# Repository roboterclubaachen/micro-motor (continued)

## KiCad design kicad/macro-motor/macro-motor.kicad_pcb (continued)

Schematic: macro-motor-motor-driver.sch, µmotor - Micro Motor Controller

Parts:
C301: >10µ 35V; CP_Radial_D8.0mm_P3.50mm
C302: 100n 50V; C_0603_1608Metric
C303: 100n 50V; C_0402_1005Metric
C304: 1µ 6V3 X7R; C_0402_1005Metric
C305: 1µ 16V X7R; C_0402_1005Metric
C306: 47n 50V X7R; C_0402_1005Metric
J301: A; PinHeader_1x02_P2.54mm_Vertical
J302: B; PinHeader_1x02_P2.54mm_Vertical
J303: C; PinHeader_1x02_P2.54mm_Vertical
JP301: SPC; SolderJumper-2_P1.3mm_Open_RoundedPad1.0x1.5mm
JP302: SPB; SolderJumper-2_P1.3mm_Open_RoundedPad1.0x1.5mm
JP303: SPA; SolderJumper-2_P1.3mm_Open_RoundedPad1.0x1.5mm
Q301, Q302, Q303: FDMD82xx; DFN-12-2EP_3.3x5mm_Pitch0.65mm
R301: 10k; R_0402_1005Metric
R302, R303, R304: 5m; R_0805_2012Metric
TP301: +24V; Pin_D1.0mm_L10.0mm
TP302: GND; Pin_D1.0mm_L10.0mm
TP303, TP304: UP; Pin_D1.0mm_L10.0mm
TP305: VP; Pin_D1.0mm_L10.0mm
TP306: VN; Pin_D1.0mm_L10.0mm
TP307: WP; Pin_D1.0mm_L10.0mm
TP308: WN; Pin_D1.0mm_L10.0mm
TP309: MOSI; Pin_D1.0mm_L10.0mm
TP310: MISO; Pin_D1.0mm_L10.0mm
TP311: SCK; Pin_D1.0mm_L10.0mm
TP312: ~CS; Pin_D1.0mm_L10.0mm
TP313, TP322: W; Pin_D1.0mm_L10.0mm
TP314, TP323: V; Pin_D1.0mm_L10.0mm
TP315, TP324: U; Pin_D1.0mm_L10.0mm
TP316: GH_U; Pin_D1.0mm_L10.0mm
TP317: GL_U; Pin_D1.0mm_L10.0mm
TP318: GH_W; Pin_D1.0mm_L10.0mm
TP319: GL_W; Pin_D1.0mm_L10.0mm
TP320: GH_V; Pin_D1.0mm_L10.0mm
TP321: GL_V; Pin_D1.0mm_L10.0mm
U301: DRV8323S; QFN-40-1EP_6x6mm_P0.5mm_EP4.6x4.6mm

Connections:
+3V3: R301.2, U301.24 (VREF); also elsewhere on the board
+24V: C301.1, C302.1, C303.1, C305.2, Q301.1 (D1), Q301.2, Q301.3, Q301.13 (D1), Q302.1 (D1), Q302.2, Q302.3, Q302.13 (D1), Q303.1 (D1), Q303.2, Q303.3, Q303.13 (D1), TP301.1, U301.4 (VM), U301.5 (VDRAIN); also elsewhere on the board
/Microcontroller/CS: TP312.1, U301.29 (~SCS); also elsewhere on the board
/Microcontroller/CurrentU: TP315.1, U301.23 (SOA); also elsewhere on the board
/Microcontroller/CurrentV: TP314.1, U301.22 (SOB); also elsewhere on the board
/Microcontroller/CurrentW: TP313.1, U301.21 (SOC); also elsewhere on the board
/Microcontroller/Fault: U301.25 (~FAULT); also elsewhere on the board
/Microcontroller/MISO: R301.1, TP310.1, U301.26 (SDO); also elsewhere on the board
/Microcontroller/MOSI: TP309.1, U301.27 (SDI); also elsewhere on the board
/Microcontroller/SCK: TP311.1, U301.28 (SCLK); also elsewhere on the board
/Motor_Driver/3V3_DRV: C304.2, U301.33 (DVDD)
/Motor_Driver/CPH: C306.2, U301.2 (CPH)
/Motor_Driver/CPL: C306.1, U301.1 (CPL)
/Motor_Driver/ENABLE: U301.30 (ENABLE); also elsewhere on the board
/Motor_Driver/GH_U: Q303.12 (G1), TP316.1, U301.6 (GHA)
/Motor_Driver/GH_V: Q302.12 (G1), TP320.1, U301.15 (GHB)
/Motor_Driver/GH_W: Q301.12 (G1), TP318.1, U301.16 (GHC)
/Motor_Driver/GL_U: Q303.4 (G2), TP317.1, U301.8 (GLA)
/Motor_Driver/GL_V: Q302.4 (G2), TP321.1, U301.13 (GLB)
/Motor_Driver/GL_W: Q301.4 (G2), TP319.1, U301.18 (GLC)
/Motor_Driver/IN_U_N: TP304.1, U301.35 (INLA); also elsewhere on the board
/Motor_Driver/IN_U_P: TP303.1, U301.34 (INHA); also elsewhere on the board
/Motor_Driver/IN_V_N: TP306.1, U301.37 (INLB); also elsewhere on the board
/Motor_Driver/IN_V_P: TP305.1, U301.36 (INHB); also elsewhere on the board
/Motor_Driver/IN_W_N: TP308.1, U301.39 (INLC); also elsewhere on the board
/Motor_Driver/IN_W_P: TP307.1, U301.38 (INHC); also elsewhere on the board
/Motor_Driver/OUT_U: Q303.7, Q303.8, Q303.9, Q303.10, Q303.11 (G1R), TP324.1, U301.7 (SHA); also elsewhere on the board
/Motor_Driver/OUT_V: Q302.7, Q302.8, Q302.9, Q302.10, Q302.11 (G1R), TP323.1, U301.14 (SHB); also elsewhere on the board
/Motor_Driver/OUT_W: Q301.7, Q301.8, Q301.9, Q301.10, Q301.11 (G1R), TP322.1, U301.17 (SHC); also elsewhere on the board
/Motor_Driver/VCP: C305.1, U301.3 (VCP)
GND: C301.2, C302.2, C303.2, C304.1, J303.2, R304.2, TP302.1, U301.10 (SNA), U301.31 (CAL), U301.32 (AGND), U301.40 (PGND), U301.41 (GND); also elsewhere on the board
unnamed: J301.1, JP301.2, Q301.5 (S2), Q301.6, Q301.14 (S2), R302.1
unnamed: J301.2, J302.2, J303.1, JP303.2, Q303.5 (S2), Q303.6, Q303.14 (S2), R302.2, R303.2, R304.1, U301.11 (SNB), U301.20 (SNC)
unnamed: J302.1, JP302.2, Q302.5 (S2), Q302.6, Q302.14 (S2), R303.1
unnamed: JP301.1, U301.19 (SPC)
unnamed: JP302.1, U301.12 (SPB)
unnamed: JP303.1, U301.9 (SPA)

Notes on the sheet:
Calibration can be done via SPI
Optional: SHx pins will be used for SPx (DRV8323S CSA_FET bit)
external capacitor >10µ 35V connected to pads

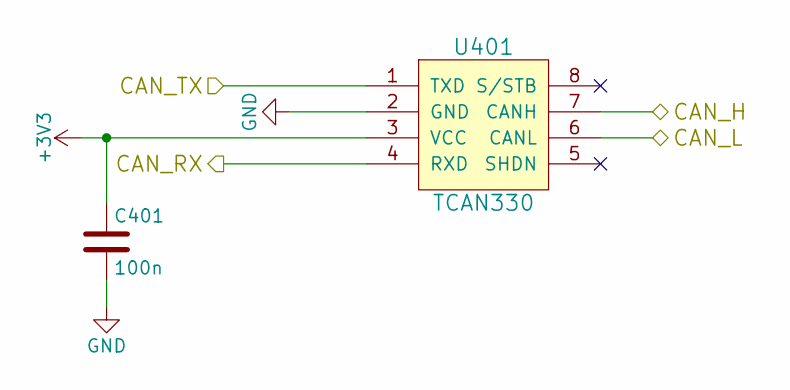
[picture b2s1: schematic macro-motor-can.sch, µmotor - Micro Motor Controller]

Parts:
C401: 100n; C_0402_1005Metric
U401: TCAN330; SOT-23-8

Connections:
+3V3: C401.1, U401.3 (VCC); also elsewhere on the board
/CAN/CAN_H: U401.7 (CANH); also elsewhere on the board
/CAN/CAN_L: U401.6 (CANL); also elsewhere on the board
/CAN/CAN_RX: U401.4 (RXD); also elsewhere on the board
/CAN/CAN_TX: U401.1 (TXD); also elsewhere on the board
GND: C401.2, U401.2 (GND); also elsewhere on the board

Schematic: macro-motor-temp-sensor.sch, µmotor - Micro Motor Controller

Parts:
C501: 100n; C_0402_1005Metric
J501: SCL; Pin_D1.0mm_L10.0mm
J502: SDA; Pin_D1.0mm_L10.0mm
J503: 3V3; Pin_D1.0mm_L10.0mm
J504: GND; Pin_D1.0mm_L10.0mm
R501, R502: 4k7; R_0402_1005Metric
U501: TMP006; WCSP-8_1.6x1.6mm_P0.5mm

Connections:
+3V3: C501.1, J503.1, R501.1, R502.1, U501.A3 (V+); also elsewhere on the board
/Microcontroller/I2C_SCL: J501.1, R501.2, U501.B3 (SCL); also elsewhere on the board
/Microcontroller/I2C_SDA: J502.1, R502.2, U501.C3 (SDA); also elsewhere on the board
GND: C501.2, J504.1, U501.A1 (DGND), U501.A2 (AGND), U501.B1 (ADR1), U501.C1 (ADR0); also elsewhere on the board

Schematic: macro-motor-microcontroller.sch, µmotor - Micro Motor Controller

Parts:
C601, C602, C603: 100n; C_0402_1005Metric
D601: Blue; LED_0402_1005Metric
D602: Red; LED_0402_1005Metric
J601: SWD; PinHeader_1x03_P2.54mm_Vertical
J604: UART; PinHeader_1x03_P2.54mm_Vertical
J605: OP_INM; Pin_D1.0mm_L10.0mm
J606: OP_OUT; Pin_D1.0mm_L10.0mm
J607: PA0; Pin_D1.0mm_L10.0mm
J608: PH1; Pin_D1.0mm_L10.0mm
J609: PH0; Pin_D1.0mm_L10.0mm
R601, R602, R604: 1k; R_0402_1005Metric
R603, R605, R606, R607, R608: 10k; R_0402_1005Metric
U601: STM32L433C(B-C)Ux_u; QFN-48-1EP_7x7mm_P0.5mm_EP5.6x5.6mm

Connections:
+3V3: C602.1, C603.1, R601.2, U601.1 (VBAT), U601.9 (VDDA/VREF+), U601.24 (VDD), U601.36 (VDDUSB), U601.48 (VDD); also elsewhere on the board
+24V: R603.2; also elsewhere on the board
/CAN/CAN_RX: U601.45 (PB8/CAN1_RX/I2C1_SCL/LCD_SEG16/SAI1_MCL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); also elsewhere on the board
/CAN/CAN_TX: U601.46 (PB9/CAN1_TX/DAC1_EXTI9/I2C1_SDA/IR_OUT/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); also elsewhere on the board
/Encoder/A: U601.38 (PA15(JTDI)/ADC1_EXTI15/LCD_SEG17/SPI1_N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); also elsewhere on the board
/Encoder/B: U601.39 (PB3(JTDO-TRACESWO)/COMP2_INM/LCD_SEG7/S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); also elsewhere on the board
/Microcontroller/BemfU: U601.17 (PA7/ADC1_IN12/COMP2_OUT/I2C3_SCL/LCD_SE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); also elsewhere on the board
/Microcontroller/BemfV: U601.18 (PB0/ADC1_IN15/COMP1_OUT/LCD_SEG5/QUADSP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); also elsewhere on the board
/Microcontroller/BemfW: U601.19 (PB1/ADC1_IN16/COMP1_INM/LCD_SEG6/LPTIM2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); also elsewhere on the board
/Microcontroller/CS: U601.33 (PA12/CAN1_TX/SPI1_MOSI/TIM1_ETR/USART1_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); also elsewhere on the board
/Microcontroller/CurrentU: R605.2, U601.14 (PA4/ADC1_IN9/COMP1_INM/COMP2_INM/DAC1_O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); also elsewhere on the board
/Microcontroller/CurrentV: R606.2, U601.15 (PA5/ADC1_IN10/COMP1_INM/COMP2_INM/DAC1_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); also elsewhere on the board
/Microcontroller/CurrentW: R607.2; also elsewhere on the board
/Microcontroller/Fault: U601.40 (PB4(NJTRST)/COMP2_INP/I2C3_SDA/LCD_SEG8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); also elsewhere on the board
/Microcontroller/Gpio: U601.20 (PB2/COMP1_INP/I2C3_SMBA/LCD_VLCD/LPTIM1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); also elsewhere on the board
/Microcontroller/HallU: U601.2 (PC13/RTC_OUT_ALARM/RTC_OUT_CALIB/RTC_TA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); also elsewhere on the board
/Microcontroller/HallV: U601.3 (PC14-OSC32_IN(PC14)/RCC_OSC32_IN); also elsewhere on the board
/Microcontroller/HallW: U601.4 (PC15-OSC32_OUT(PC15)/ADC1_EXTI15/RCC_OS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); also elsewhere on the board
/Microcontroller/I2C_SCL: U601.21 (PB10/COMP1_OUT/I2C2_SCL/LCD_SEG10/LPUAR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); also elsewhere on the board
/Microcontroller/I2C_SDA: U601.22 (PB11/ADC1_EXTI11/COMP2_OUT/I2C2_SDA/LCD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); also elsewhere on the board
/Microcontroller/Led: D601.1 (K), D602.2 (A), U601.25 (PB12/I2C2_SMBA/LCD_SEG12/LPUART1_DE/LPU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)
/Microcontroller/LedCom: D601.2 (A), D602.1 (K), R601.1, R602.2
/Microcontroller/MISO: U601.43 (PB7/COMP2_INM/I2C1_SDA/LCD_SEG21/LPTIM1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); also elsewhere on the board
/Microcontroller/MOSI: U601.42 (PB6/COMP2_INP/I2C1_SCL/LPTIM1_ETR/SAI1_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); also elsewhere on the board
/Microcontroller/OP_INM: J605.1, R605.1, R606.1, R607.1, R608.2, U601.11 (PA1/ADC1_IN6/COMP1_INP/I2C1_SMBA/LCD_SE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)
/Microcontroller/OP_OUT: J606.1, R608.1, U601.13 (PA3/ADC1_IN8/COMP2_INP/LCD_SEG2/LPUART1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)
/Microcontroller/PA0: J607.1, U601.10 (PA0/ADC1_IN5/COMP1_INM/COMP1_OUT/OPAMP1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)
/Microcontroller/PH0: J609.1, U601.5 (PH0-OSC_IN(PH0)/RCC_OSC_IN)
/Microcontroller/PH1: J608.1, U601.6 (PH1-OSC_OUT(PH1)/RCC_OSC_OUT)
/Microcontroller/SCK: U601.41 (PB5/COMP2_OUT/I2C1_SMBA/LCD_SEG9/LPTIM1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); also elsewhere on the board
/Microcontroller/SWCLK: J601.1, U601.37 (PA14(JTCK-SWCLK)/I2C1_SMBA/LPTIM1_OUT/S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)
/Microcontroller/SWDIO: J601.3, U601.34 (PA13(JTMS-SWDIO)/IR_OUT/SAI1_SD_B/SWPMI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)
/Microcontroller/TX: J604.3, U601.12 (PA2/ADC1_IN7/COMP2_INM/COMP2_OUT/LCD_SE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)
/Microcontroller/~RST: C601.1, U601.7 (NRST)
/Motor_Driver/ENABLE: U601.32 (PA11/ADC1_EXTI11/CAN1_RX/COMP1_OUT/SPI1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); also elsewhere on the board
/Motor_Driver/IN_U_N: U601.26 (PB13/I2C2_SCL/LCD_SEG13/LPUART1_CTS/SAI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); also elsewhere on the board
/Motor_Driver/IN_U_P: U601.29 (PA8/LCD_COM0/LPTIM2_OUT/RCC_MCO/SAI1_SC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); also elsewhere on the board
/Motor_Driver/IN_V_N: U601.27 (PB14/I2C2_SDA/LCD_SEG14/SAI1_MCLK_A/SPI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); also elsewhere on the board
/Motor_Driver/IN_V_P: U601.30 (PA9/DAC1_EXTI9/I2C1_SCL/LCD_COM1/SAI1_F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); also elsewhere on the board
/Motor_Driver/IN_W_N: U601.28 (PB15/ADC1_EXTI15/LCD_SEG15/RTC_REFIN/SA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); also elsewhere on the board
/Motor_Driver/IN_W_P: U601.31 (PA10/CRS_SYNC/I2C1_SDA/LCD_COM2/SAI1_SD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); also elsewhere on the board
GND: C601.2, C602.2, C603.2, J601.2, J604.1, R602.1, R604.1, U601.8 (VSSA/VREF-), U601.23 (VSS), U601.35 (VSS), U601.44 (PH3-BOOT0), U601.47 (VSS), U601.49 (Pad); also elsewhere on the board
unnamed: R603.1, R604.2, U601.16 (PA6/ADC1_IN11/COMP1_OUT/LCD_SEG3/LPUART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)

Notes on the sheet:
Debug LEDs
STM32 OPAMP
-IN OUT +IN
+IN: Virtual ground (Vcc/2) by DAC
Supply voltage measure 1:11 voltage divider
OP_OUT is internal connected to COMP2_INP

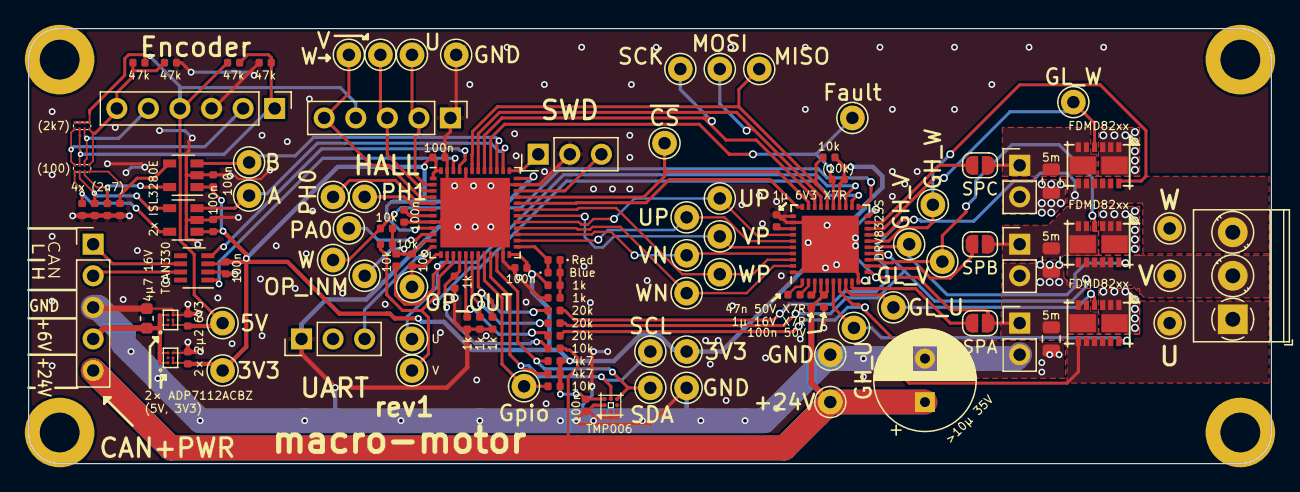
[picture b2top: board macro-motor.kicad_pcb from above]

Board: 2 copper layers, 100.0 x 35.0 mm, 116 parts (1 on the bottom side), 74 nets.

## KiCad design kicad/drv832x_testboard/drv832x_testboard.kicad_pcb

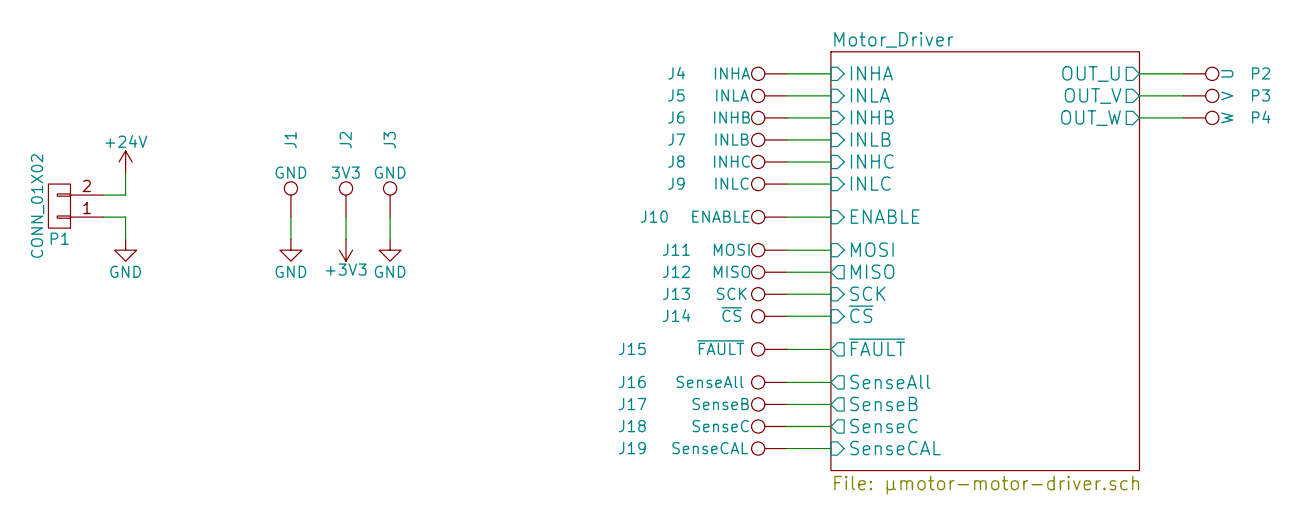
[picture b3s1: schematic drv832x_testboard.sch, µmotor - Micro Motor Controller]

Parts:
J1, J3: GND; Measurement_Point_Round-TH_Small
J2: 3V3; Measurement_Point_Round-TH_Small
J4: INHA; Measurement_Point_Round-TH_Small
J5: INLA; Measurement_Point_Round-TH_Small
J6: INHB; Measurement_Point_Round-TH_Small
J7: INLB; Measurement_Point_Round-TH_Small
J8: INHC; Measurement_Point_Round-TH_Small
J9: INLC; Measurement_Point_Round-TH_Small
J10: ENABLE; Measurement_Point_Round-TH_Small
J11: MOSI; Measurement_Point_Round-TH_Small
J12: MISO; Measurement_Point_Round-TH_Small
J13: SCK; Measurement_Point_Round-TH_Small
J14: ~CS; Measurement_Point_Round-TH_Small
J15: ~FAULT; Measurement_Point_Round-TH_Small
J16: SenseAll; Measurement_Point_Round-TH_Small
J17: SenseB; Measurement_Point_Round-TH_Small
J18: SenseC; Measurement_Point_Round-TH_Small
J19: SenseCAL; Measurement_Point_Round-TH_Small
P1: CONN_01X02; Test_Point_2Pads
P2: U; Measurement_Point_Round-TH_Big
P3: V; Measurement_Point_Round-TH_Big
P4: W; Measurement_Point_Round-TH_Big

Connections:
+3V3: J2.1; also elsewhere on the board
+24V: P1.2; also elsewhere on the board
/Motor_Driver/ENABLE: J10.1; also elsewhere on the board
/Motor_Driver/INHA: J4.1; also elsewhere on the board
/Motor_Driver/INHB: J6.1; also elsewhere on the board
/Motor_Driver/INHC: J8.1; also elsewhere on the board
/Motor_Driver/INLA: J5.1; also elsewhere on the board
/Motor_Driver/INLB: J7.1; also elsewhere on the board
/Motor_Driver/INLC: J9.1; also elsewhere on the board
/Motor_Driver/MISO: J12.1; also elsewhere on the board
/Motor_Driver/MOSI: J11.1; also elsewhere on the board
/Motor_Driver/OUT_U: P2.1; also elsewhere on the board
/Motor_Driver/OUT_V: P3.1; also elsewhere on the board
/Motor_Driver/OUT_W: P4.1; also elsewhere on the board
/Motor_Driver/SCK: J13.1; also elsewhere on the board
/Motor_Driver/SenseAll: J16.1; also elsewhere on the board
/Motor_Driver/SenseB: J17.1; also elsewhere on the board
/Motor_Driver/SenseC: J18.1; also elsewhere on the board
/Motor_Driver/SenseCAL: J19.1; also elsewhere on the board
/Motor_Driver/~CS: J14.1; also elsewhere on the board
/Motor_Driver/~FAULT: J15.1; also elsewhere on the board
GND: J1.1, J3.1, P1.1; also elsewhere on the board

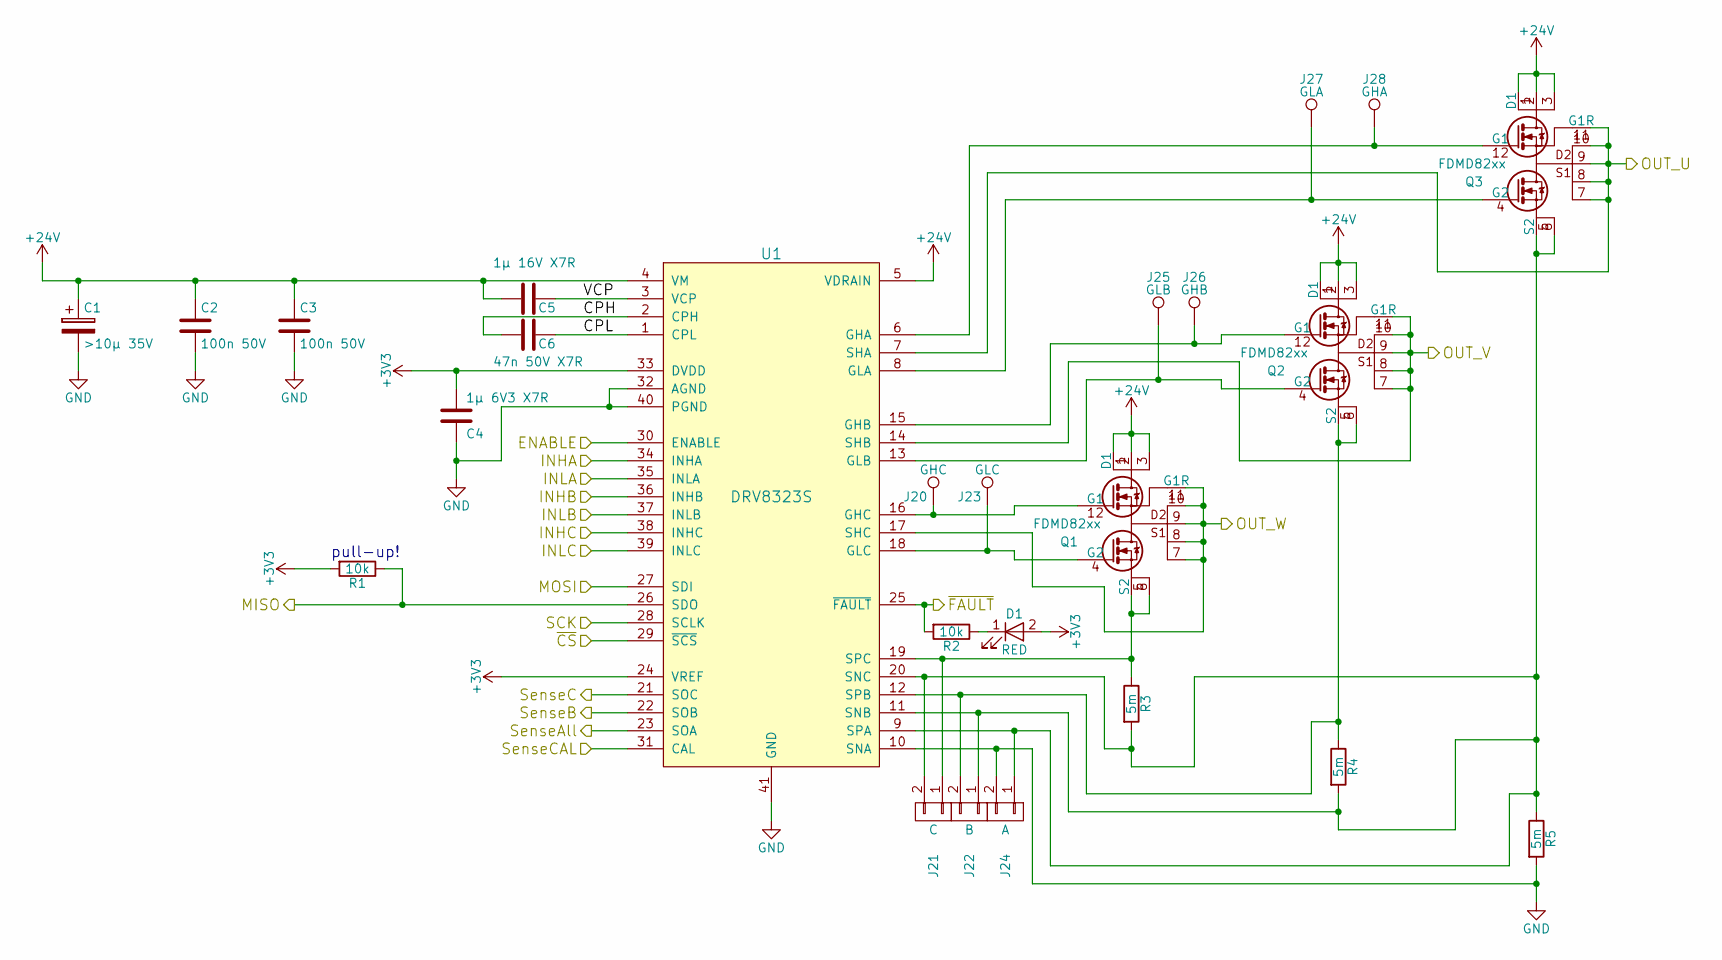
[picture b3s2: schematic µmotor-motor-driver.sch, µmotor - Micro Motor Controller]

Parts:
C1: >10µ 35V; CP_Radial_D8.0mm_P3.80mm
C2, C3: 100n 50V; C_0603
C4: 1µ 6V3 X7R; C_0603
C5: 1µ 16V X7R; C_0603
C6: 47n 50V X7R; C_0603
D1: RED; LED_0603
J20: GHC; Measurement_Point_Round-TH_Small
J21: C; Pin_Header_Straight_1x02_Pitch2.54mm
J22: B; Pin_Header_Straight_1x02_Pitch2.54mm
J23: GLC; Measurement_Point_Round-TH_Small
J24: A; Pin_Header_Straight_1x02_Pitch2.54mm
J25: GLB; Measurement_Point_Round-TH_Small
J26: GHB; Measurement_Point_Round-TH_Small
J27: GLA; Measurement_Point_Round-TH_Small
J28: GHA; Measurement_Point_Round-TH_Small
Q1, Q2, Q3: FDMD82xx; DFN-12-2EP_3.3x5mm_Pitch0.65mm
R1, R2: 10k; R_0603
R3, R4, R5: 5m; R_0805
U1: DRV8323S; QFN-40-1EP_6x6mm_Pitch0.5mm

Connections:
+3V3: C4.1, D1.2 (A), R1.2, U1.24 (VREF), U1.33 (DVDD); also elsewhere on the board
+24V: C1.1, C2.1, C3.1, C5.2, Q1.1 (D1), Q1.2, Q1.3, Q1.13 (D1), Q2.1 (D1), Q2.2, Q2.3, Q2.13 (D1), Q3.1 (D1), Q3.2, Q3.3, Q3.13 (D1), U1.4 (VM), U1.5 (VDRAIN); also elsewhere on the board
/Motor_Driver/CPH: C6.2, U1.2 (CPH)
/Motor_Driver/CPL: C6.1, U1.1 (CPL)
/Motor_Driver/ENABLE: U1.30 (ENABLE); also elsewhere on the board
/Motor_Driver/INHA: U1.34 (INHA); also elsewhere on the board
/Motor_Driver/INHB: U1.36 (INHB); also elsewhere on the board
/Motor_Driver/INHC: U1.38 (INHC); also elsewhere on the board
/Motor_Driver/INLA: U1.35 (INLA); also elsewhere on the board
/Motor_Driver/INLB: U1.37 (INLB); also elsewhere on the board
/Motor_Driver/INLC: U1.39 (INLC); also elsewhere on the board
/Motor_Driver/MISO: R1.1, U1.26 (SDO); also elsewhere on the board
/Motor_Driver/MOSI: U1.27 (SDI); also elsewhere on the board
/Motor_Driver/OUT_U: Q3.7, Q3.8, Q3.9, Q3.10, Q3.11 (G1R), U1.7 (SHA); also elsewhere on the board
/Motor_Driver/OUT_V: Q2.7, Q2.8, Q2.9, Q2.10, Q2.11 (G1R), U1.14 (SHB); also elsewhere on the board
/Motor_Driver/OUT_W: Q1.7, Q1.8, Q1.9, Q1.10, Q1.11 (G1R), U1.17 (SHC); also elsewhere on the board
/Motor_Driver/SCK: U1.28 (SCLK); also elsewhere on the board
/Motor_Driver/SenseAll: U1.23 (SOA); also elsewhere on the board
/Motor_Driver/SenseB: U1.22 (SOB); also elsewhere on the board
/Motor_Driver/SenseC: U1.21 (SOC); also elsewhere on the board
/Motor_Driver/SenseCAL: U1.31 (CAL); also elsewhere on the board
/Motor_Driver/VCP: C5.1, U1.3 (VCP)
/Motor_Driver/~CS: U1.29 (~SCS); also elsewhere on the board
/Motor_Driver/~FAULT: R2.2, U1.25 (~FAULT); also elsewhere on the board
GND: C1.2, C2.2, C3.2, C4.2, J24.2, R5.2, U1.10 (SNA), U1.32 (AGND), U1.40 (PGND), U1.41 (GND); also elsewhere on the board
unnamed: D1.1 (K), R2.1
unnamed: J20.1, Q1.12 (G1), U1.16 (GHC)
unnamed: J21.1, Q1.5 (S2), Q1.6, Q1.14 (S2), R3.1, U1.19 (SPC)
unnamed: J21.2, J22.1, J24.1, Q3.5 (S2), Q3.6, Q3.14 (S2), R3.2, R4.2, R5.1, U1.9 (SPA), U1.11 (SNB), U1.20 (SNC)
unnamed: J22.2, Q2.5 (S2), Q2.6, Q2.14 (S2), R4.1, U1.12 (SPB)
unnamed: J23.1, Q1.4 (G2), U1.18 (GLC)
unnamed: J25.1, Q2.4 (G2), U1.13 (GLB)
unnamed: J26.1, Q2.12 (G1), U1.15 (GHB)
unnamed: J27.1, Q3.4 (G2), U1.8 (GLA)
unnamed: J28.1, Q3.12 (G1), U1.6 (GHA)

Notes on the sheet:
pull-up!

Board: 2 copper layers, 48 parts (0 on the bottom side), 35 nets, no tracks yet.

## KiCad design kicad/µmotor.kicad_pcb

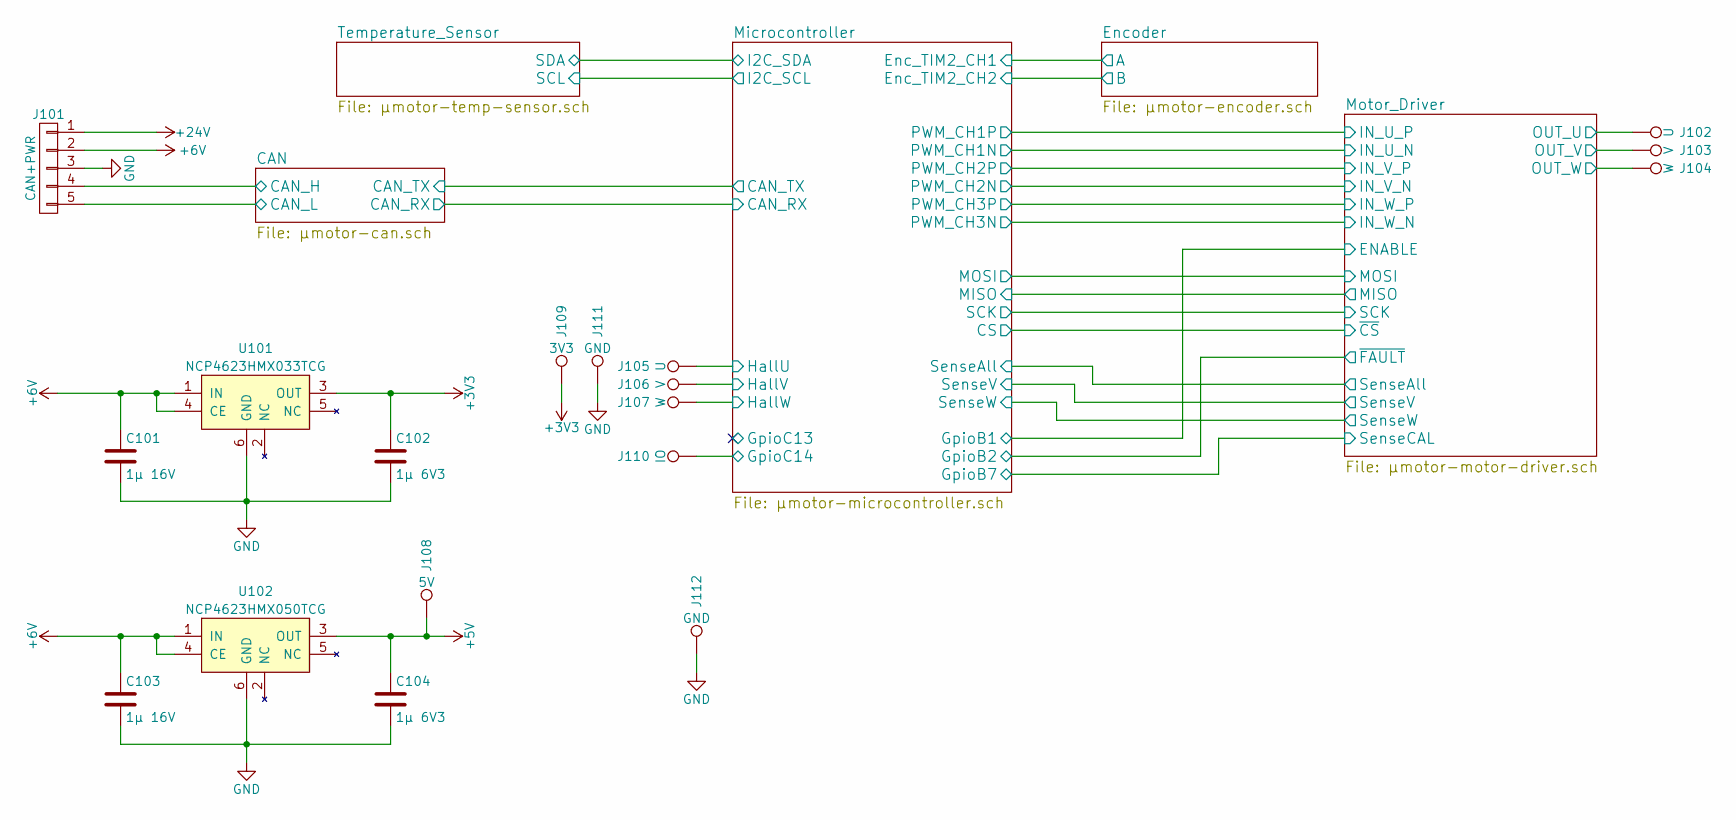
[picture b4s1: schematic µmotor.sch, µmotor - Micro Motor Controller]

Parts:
C101, C103: 1µ 16V; C_0603
C102, C104: 1µ 6V3; C_0603
J101: CAN+PWR; Pin_Header_Straight_1x05_Pitch2.54mm
J102: U; Measurement_Point_Round-TH_Small
J103: V; Measurement_Point_Round-TH_Small
J104: W; Measurement_Point_Round-TH_Small
J105: U; Measurement_Point_Round-SMD-Pad_Smaller_0.75mm
J106: V; Measurement_Point_Round-SMD-Pad_Smaller_0.75mm
J107: W; Measurement_Point_Round-SMD-Pad_Smaller_0.75mm
J108: 5V; Measurement_Point_Round-SMD-Pad_Smaller_0.75mm
J109: 3V3; Measurement_Point_Round-SMD-Pad_Smaller_0.75mm
J110: IO; Measurement_Point_Round-SMD-Pad_Smaller_0.75mm
J111, J112: GND; Measurement_Point_Round-SMD-Pad_Smaller_0.75mm
U101: NCP4623HMX033TCG; DFN-6-1EP_2x2mm_Pitch0.5mm
U102: NCP4623HMX050TCG; DFN-6-1EP_2x2mm_Pitch0.5mm

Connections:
+3V3: C102.1, J109.1, U101.3 (OUT); also elsewhere on the board
+5V: C104.1, J108.1, U102.3 (OUT)
+6V: C101.1, C103.1, J101.2, U101.1 (IN), U101.4 (CE), U102.1 (IN), U102.4 (CE); also elsewhere on the board
+24V: J101.1; also elsewhere on the board
/CAN/CAN_H: J101.4; also elsewhere on the board
/CAN/CAN_L: J101.5; also elsewhere on the board
/Microcontroller/GpioC14: J110.1; also elsewhere on the board
/Microcontroller/HallU: J105.1; also elsewhere on the board
/Microcontroller/HallV: J106.1; also elsewhere on the board
/Microcontroller/HallW: J107.1; also elsewhere on the board
/Motor_Driver/OUT_U: J102.1; also elsewhere on the board
/Motor_Driver/OUT_V: J103.1; also elsewhere on the board
/Motor_Driver/OUT_W: J104.1; also elsewhere on the board
GND: C101.2, C102.2, C103.2, C104.2, J101.3, J111.1, J112.1, U101.6 (GND), U101.7 (GND), U102.6 (GND), U102.7 (GND); also elsewhere on the board

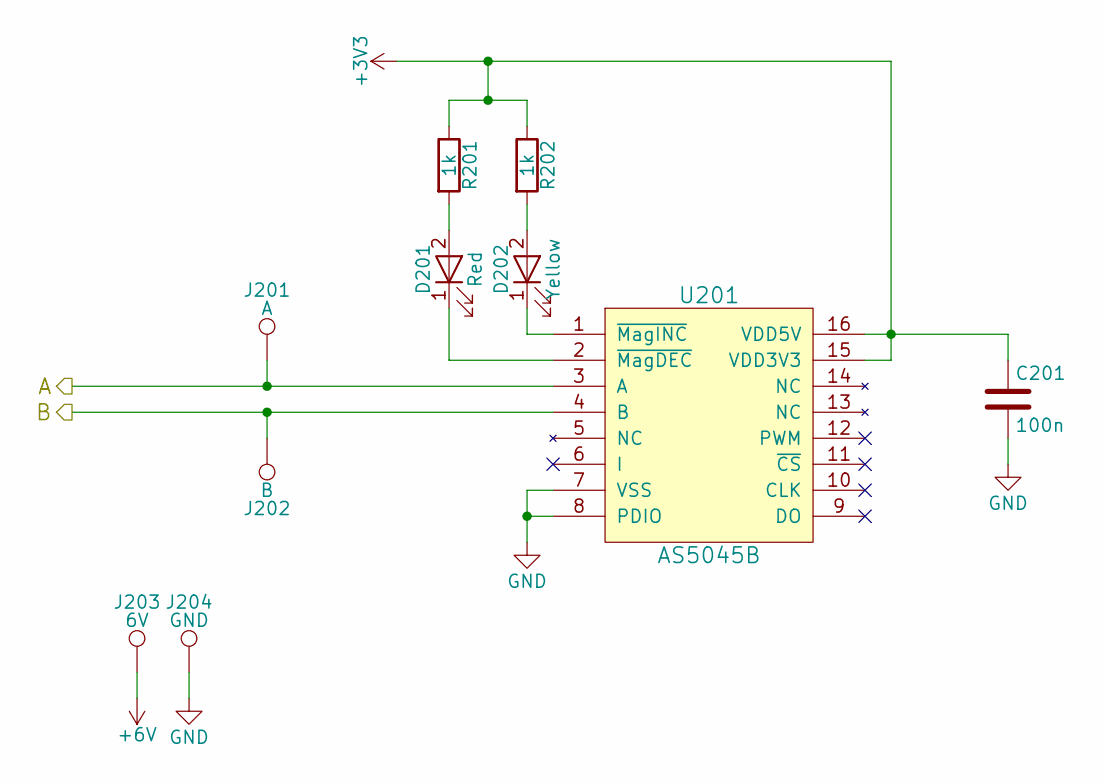
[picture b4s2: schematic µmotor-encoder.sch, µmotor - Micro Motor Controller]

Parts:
C201: 100n; C_0603
D201: Red; LED_0603
D202: Yellow; LED_0603
J201: A; Measurement_Point_Round-SMD-Pad_Smaller_0.75mm
J202: B; Measurement_Point_Round-SMD-Pad_Smaller_0.75mm
J203: 6V; Measurement_Point_Round-SMD-Pad_Smaller_0.75mm
J204: GND; Measurement_Point_Round-SMD-Pad_Smaller_0.75mm
R201, R202: 1k; R_0603
U201: AS5045B; SSOP-16_4.4x5.2mm_Pitch0.65mm

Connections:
+3V3: C201.1, R201.1, R202.1, U201.15 (VDD3V3), U201.16 (VDD5V); also elsewhere on the board
+6V: J203.1; also elsewhere on the board
/Encoder/A: J201.1, U201.3 (A); also elsewhere on the board
/Encoder/B: J202.1, U201.4 (B); also elsewhere on the board
GND: C201.2, J204.1, U201.7 (VSS), U201.8 (PDIO); also elsewhere on the board
unnamed: D201.1 (K), U201.2 (~MagDEC)
unnamed: D201.2 (A), R201.2
unnamed: D202.1 (K), U201.1 (~MagINC)
unnamed: D202.2 (A), R202.2

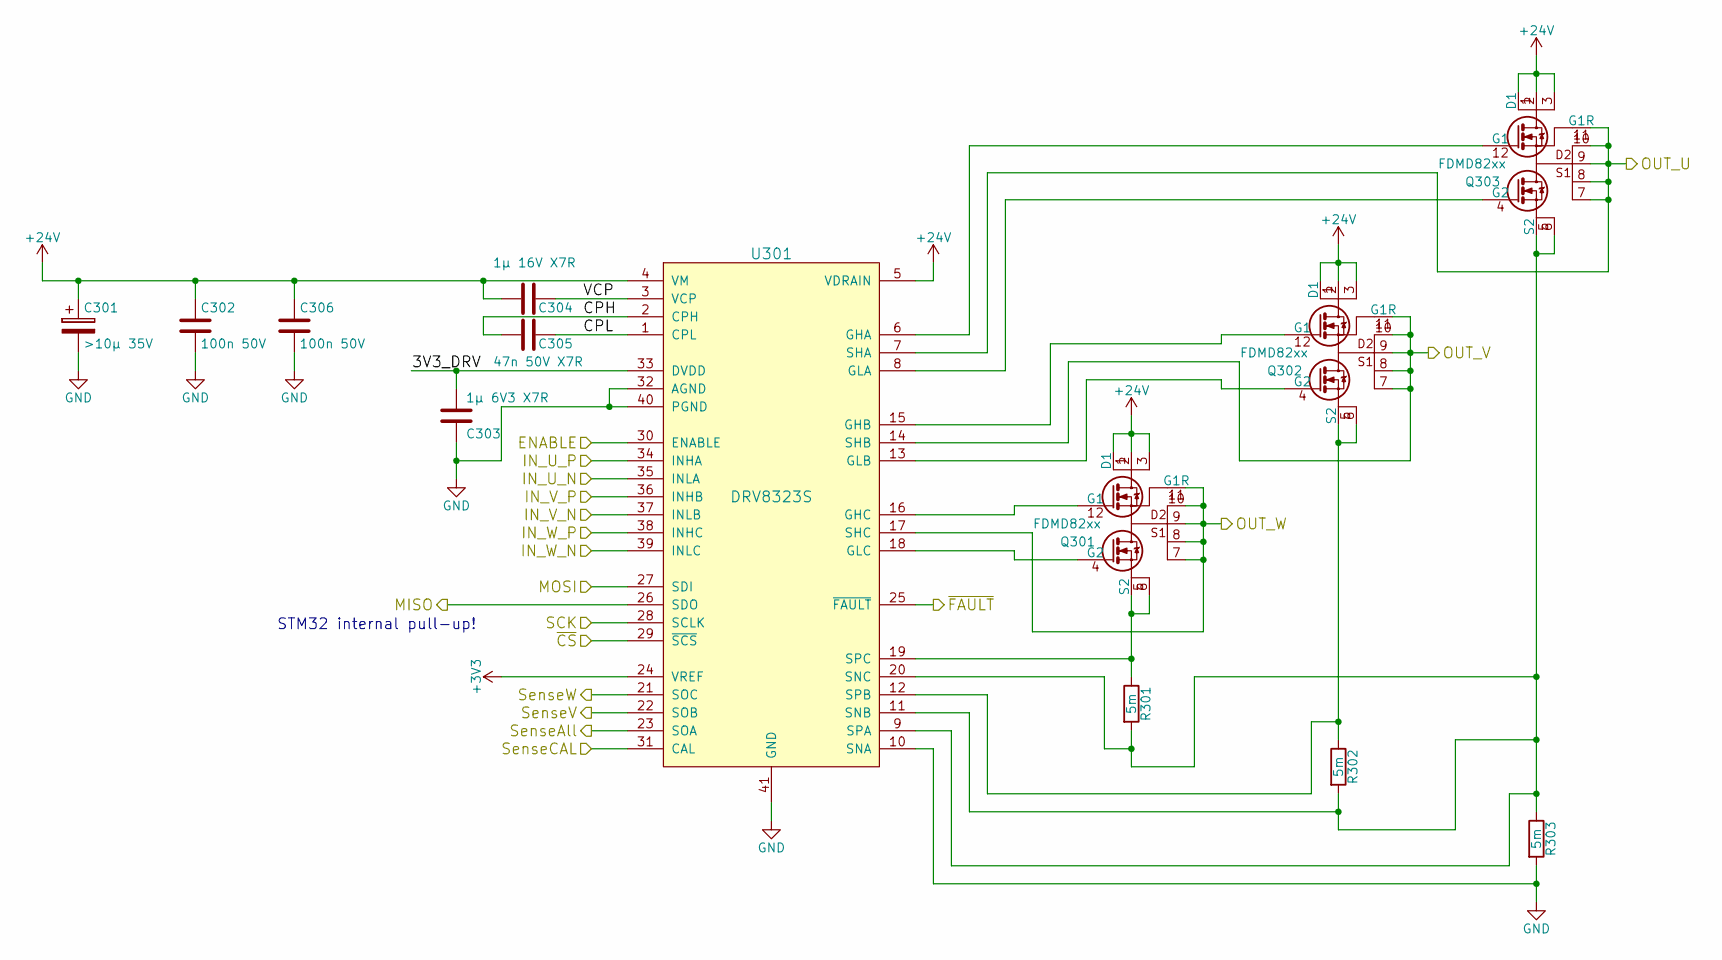
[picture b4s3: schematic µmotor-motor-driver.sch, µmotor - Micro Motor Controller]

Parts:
C301: >10µ 35V; CP_Radial_D4.0mm_P2.00mm
C302, C306: 100n 50V; C_0603
C303: 1µ 6V3 X7R; C_0603
C304: 1µ 16V X7R; C_0603
C305: 47n 50V X7R; C_0603
Q301, Q302, Q303: FDMD82xx; DFN-12-2EP_3.3x5mm_Pitch0.65mm
R301, R302, R303: 5m; R_0805
U301: DRV8323S; QFN-40-1EP_6x6mm_Pitch0.5mm

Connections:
+3V3: U301.24 (VREF); also elsewhere on the board
+24V: C301.1, C302.1, C304.2, C306.1, Q301.1 (D1), Q301.2, Q301.3, Q301.13 (D1), Q302.1 (D1), Q302.2, Q302.3, Q302.13 (D1), Q303.1 (D1), Q303.2, Q303.3, Q303.13 (D1), U301.4 (VM), U301.5 (VDRAIN); also elsewhere on the board
/Microcontroller/CS: U301.29 (~SCS); also elsewhere on the board
/Microcontroller/GpioB2: U301.25 (~FAULT); also elsewhere on the board
/Microcontroller/GpioB7: U301.31 (CAL); also elsewhere on the board
/Microcontroller/MISO: U301.26 (SDO); also elsewhere on the board
/Microcontroller/MOSI: U301.27 (SDI); also elsewhere on the board
/Microcontroller/SCK: U301.28 (SCLK); also elsewhere on the board
/Microcontroller/SenseAll: U301.23 (SOA); also elsewhere on the board
/Microcontroller/SenseV: U301.22 (SOB); also elsewhere on the board
/Microcontroller/SenseW: U301.21 (SOC); also elsewhere on the board
/Motor_Driver/3V3_DRV: C303.1, U301.33 (DVDD)
/Motor_Driver/CPH: C305.2, U301.2 (CPH)
/Motor_Driver/CPL: C305.1, U301.1 (CPL)
/Motor_Driver/ENABLE: U301.30 (ENABLE); also elsewhere on the board
/Motor_Driver/IN_U_N: U301.35 (INLA); also elsewhere on the board
/Motor_Driver/IN_U_P: U301.34 (INHA); also elsewhere on the board
/Motor_Driver/IN_V_N: U301.37 (INLB); also elsewhere on the board
/Motor_Driver/IN_V_P: U301.36 (INHB); also elsewhere on the board
/Motor_Driver/IN_W_N: U301.39 (INLC); also elsewhere on the board
/Motor_Driver/IN_W_P: U301.38 (INHC); also elsewhere on the board
/Motor_Driver/OUT_U: Q303.7, Q303.8, Q303.9, Q303.10, Q303.11 (G1R), U301.7 (SHA); also elsewhere on the board
/Motor_Driver/OUT_V: Q302.7, Q302.8, Q302.9, Q302.10, Q302.11 (G1R), U301.14 (SHB); also elsewhere on the board
/Motor_Driver/OUT_W: Q301.7, Q301.8, Q301.9, Q301.10, Q301.11 (G1R), U301.17 (SHC); also elsewhere on the board
/Motor_Driver/VCP: C304.1, U301.3 (VCP)
GND: C301.2, C302.2, C303.2, C306.2, R303.2, U301.10 (SNA), U301.32 (AGND), U301.40 (PGND), U301.41 (GND); also elsewhere on the board
unnamed: Q301.4 (G2), U301.18 (GLC)
unnamed: Q301.12 (G1), U301.16 (GHC)
unnamed: Q301.5 (S2), Q301.6, Q301.14 (S2), R301.1, U301.19 (SPC)
unnamed: Q302.4 (G2), U301.13 (GLB)
unnamed: Q302.12 (G1), U301.15 (GHB)
unnamed: Q302.5 (S2), Q302.6, Q302.14 (S2), R302.1, U301.12 (SPB)
unnamed: Q303.4 (G2), U301.8 (GLA)
unnamed: Q303.12 (G1), U301.6 (GHA)
unnamed: Q303.5 (S2), Q303.6, Q303.14 (S2), R301.2, R302.2, R303.1, U301.9 (SPA), U301.11 (SNB), U301.20 (SNC)

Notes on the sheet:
STM32 internal pull-up!

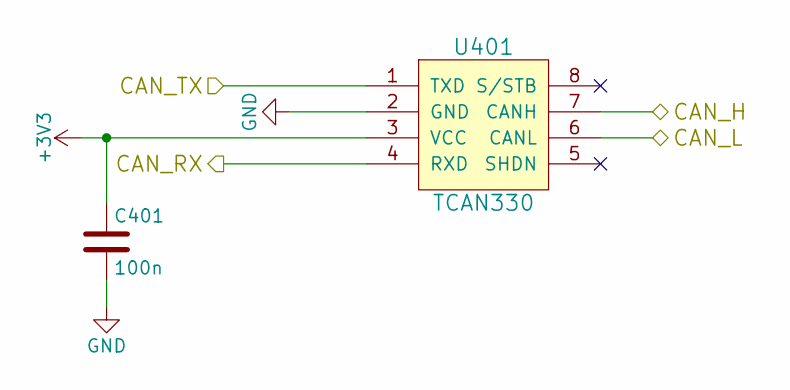
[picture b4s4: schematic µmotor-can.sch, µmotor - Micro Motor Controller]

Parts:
C401: 100n; C_0603
U401: TCAN330; SOT-23-8

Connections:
+3V3: C401.1, U401.3 (VCC); also elsewhere on the board
/CAN/CAN_H: U401.7 (CANH); also elsewhere on the board
/CAN/CAN_L: U401.6 (CANL); also elsewhere on the board
/CAN/CAN_RX: U401.4 (RXD); also elsewhere on the board
/CAN/CAN_TX: U401.1 (TXD); also elsewhere on the board
GND: C401.2, U401.2 (GND); also elsewhere on the board

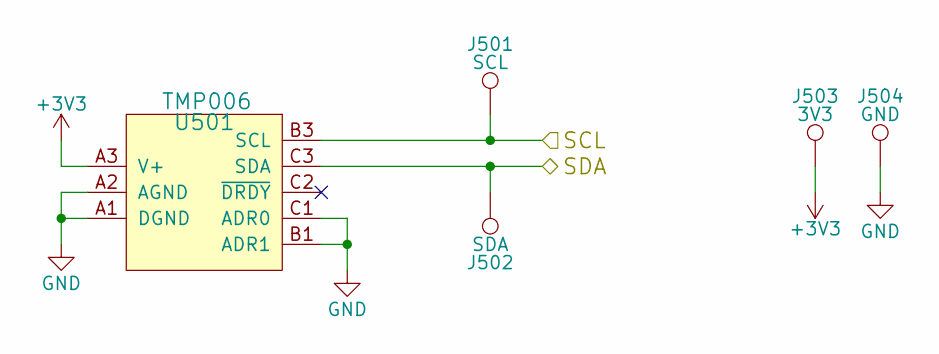
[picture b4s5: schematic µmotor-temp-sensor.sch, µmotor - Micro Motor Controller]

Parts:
J501: SCL; Measurement_Point_Round-SMD-Pad_Smaller_0.75mm
J502: SDA; Measurement_Point_Round-SMD-Pad_Smaller_0.75mm
J503: 3V3; Measurement_Point_Round-SMD-Pad_Smaller_0.75mm
J504: GND; Measurement_Point_Round-SMD-Pad_Smaller_0.75mm
U501: TMP006; WCSP-8_1.6x1.6mm_P0.5mm

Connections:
+3V3: J503.1, U501.A3 (V+); also elsewhere on the board
/Microcontroller/I2C_SCL: J501.1, U501.B3 (SCL); also elsewhere on the board
/Microcontroller/I2C_SDA: J502.1, U501.C3 (SDA); also elsewhere on the board
GND: J504.1, U501.A1 (DGND), U501.A2 (AGND), U501.B1 (ADR1), U501.C1 (ADR0); also elsewhere on the board
